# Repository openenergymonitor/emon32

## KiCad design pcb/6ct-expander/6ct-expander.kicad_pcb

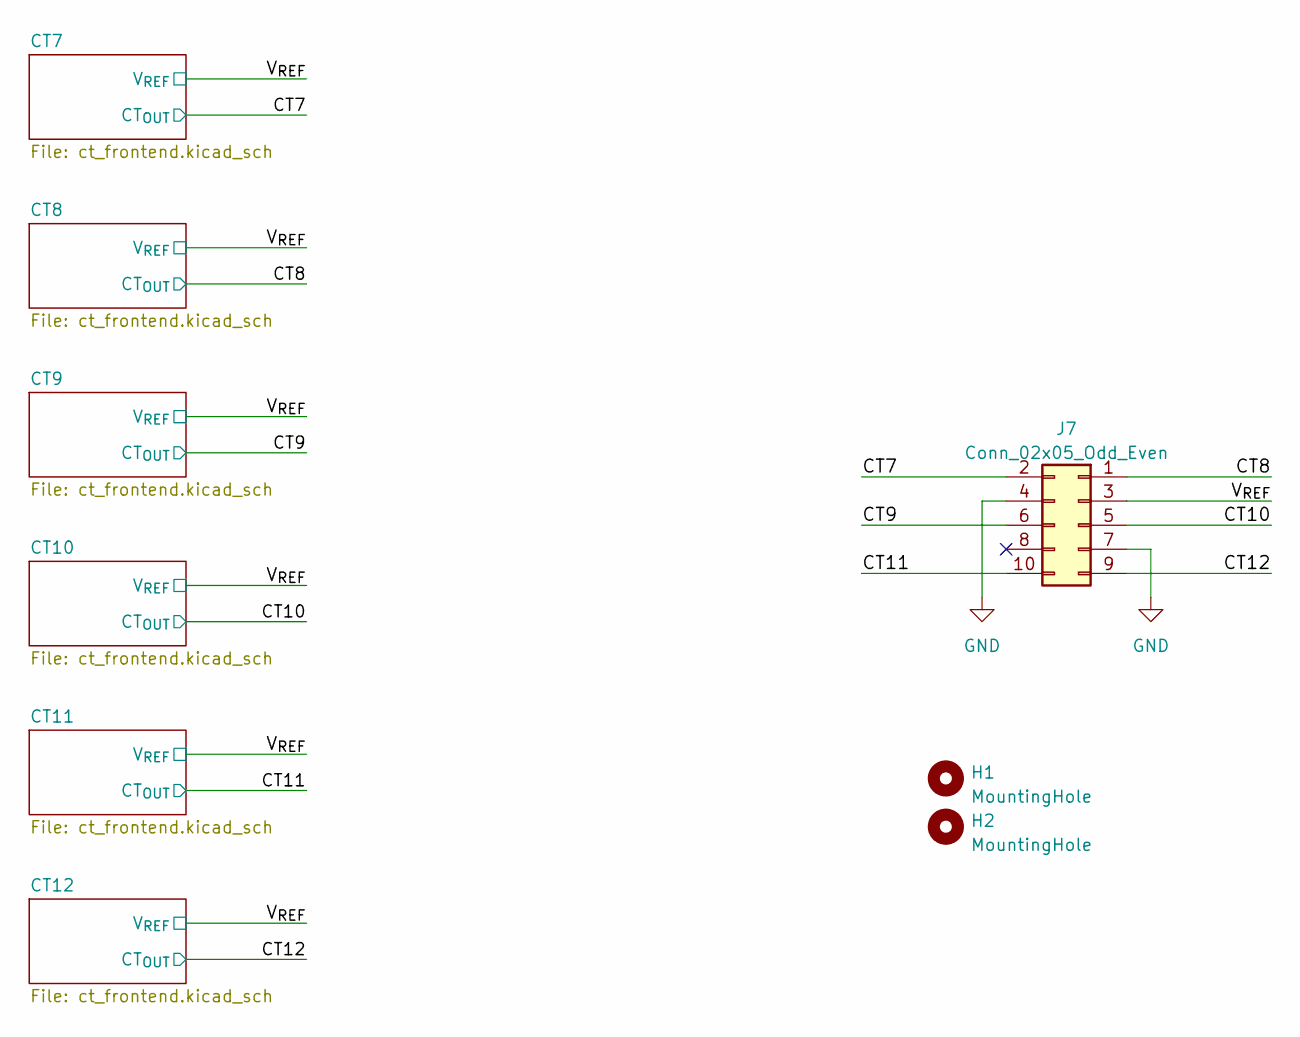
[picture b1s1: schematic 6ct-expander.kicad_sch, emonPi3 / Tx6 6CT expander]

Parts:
H1, H2: MountingHole; MountingHole_2.7mm_M2.5
J7: Conn_02x05_Odd_Even; PinHeader_2x05_P2.54mm_Vertical

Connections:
/CT7: J7.2; also elsewhere on the board
/CT8: J7.1; also elsewhere on the board
/CT9: J7.6; also elsewhere on the board
/CT10: J7.5; also elsewhere on the board
/CT11: J7.10; also elsewhere on the board
/CT12: J7.9; also elsewhere on the board
/V_{REF}: J7.3; also elsewhere on the board
GND: J7.4, J7.7; also elsewhere on the board

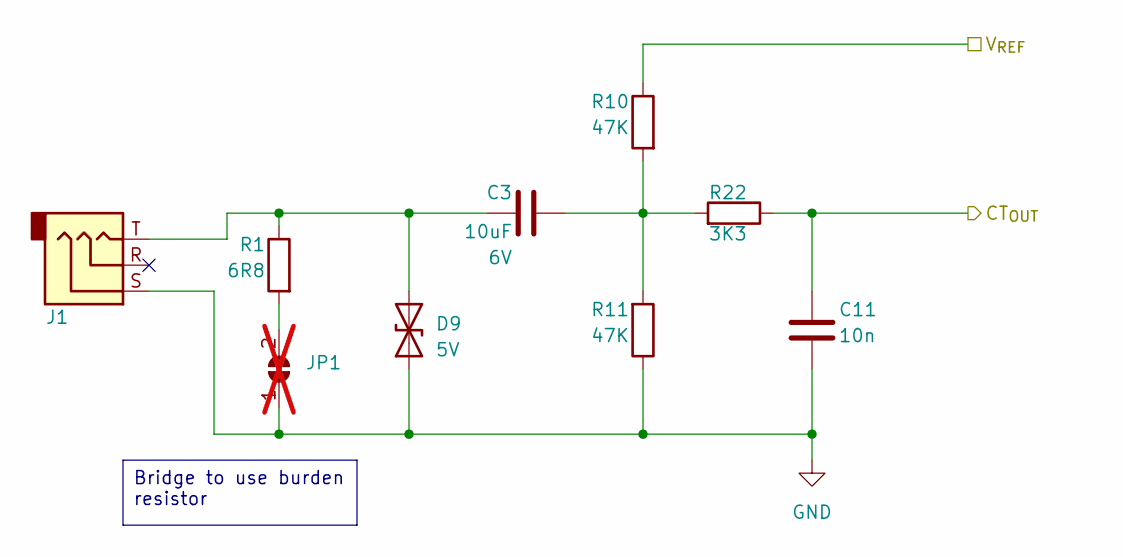
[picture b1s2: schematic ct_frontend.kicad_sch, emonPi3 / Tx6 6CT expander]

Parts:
C3: 10uF; C_0603_1608Metric; Voltage 6V; LCSC C19702
C11: 10n; C_0603_1608Metric; LCSC C57112
D9: 5V; D_SOD-523; MPN DF2B7AE,H3F; Mouser 757-DF2B7AEH3F
J1: SJ-3524-SMT-TR; Jack_3.5mm_CUI_SJ-3524-SMT_Horizontal; LCSC C4991872
JP1: SolderJumper_2_Open; SolderJumper-2_P1.3mm_Open_TrianglePad1.0x1.5mm; not fitted
R1: 6R8; R_1206_3216Metric; LCSC C25345
R10, R11: 47K; R_0603_1608Metric; LCSC C23162
R22: 3K3; R_0603_1608Metric; LCSC C22978

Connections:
/CT7: C11.1, R22.1; also elsewhere on the board
/V_{REF}: R10.1; also elsewhere on the board
GND: C11.2, D9.1 (A1), J1.S, JP1.1 (A), R11.1; also elsewhere on the board
unnamed: C3.2, R10.2, R11.2, R22.2
unnamed: C3.1, D9.2 (A2), J1.T, R1.1
unnamed: JP1.2 (B), R1.2

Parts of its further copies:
C1, C4, C6, C8, C10: 10uF; C_0603_1608Metric; Voltage 6V; LCSC C19702
C2, C5, C7, C9, C12: 10n; C_0603_1608Metric; LCSC C57112
D1, D2, D3, D4, D5: 5V; D_SOD-523; MPN DF2B7AE,H3F; Mouser 757-DF2B7AEH3F
J2, J3, J4, J5, J6: SJ-3524-SMT-TR; Jack_3.5mm_CUI_SJ-3524-SMT_Horizontal; LCSC C4991872
JP2, JP3, JP4, JP5, JP6: SolderJumper_2_Open; SolderJumper-2_P1.3mm_Open_TrianglePad1.0x1.5mm; not fitted
R2, R6: 6R8; R_1206_3216Metric; LCSC C25345
R3, R4, R7, R8, R13, R14, R17, R18, R21, R23: 47K; R_0603_1608Metric; LCSC C23162
R5, R9: 3K3; R_0603_1608Metric; LCSC C22978

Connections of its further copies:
/CT8: C2.1, R5.1; also elsewhere on the board
/CT9: C5.1, R9.1; also elsewhere on the board
/CT10: C7.1; also elsewhere on the board
/CT11: C9.1; also elsewhere on the board
/CT12: C12.1; also elsewhere on the board
/V_{REF}: R3.1, R7.1, R13.1, R17.1, R21.1; also elsewhere on the board
GND: C2.2, C5.2, C7.2, C9.2, C12.2, D1.1 (A1), D2.1 (A1), D3.1 (A1), D4.1 (A1), D5.1 (A1), J2.S, J3.S, J4.S, J5.S, J6.S, JP2.1 (A), JP3.1 (A), JP4.1 (A), JP5.1 (A), JP6.1 (A), R4.1, R8.1, R14.1, R18.1, R23.1; also elsewhere on the board
unnamed: C1.2, R3.2, R4.2, R5.2
unnamed: C4.2, R7.2, R8.2, R9.2
unnamed 11: C6.2, R13.2, R14.2; also elsewhere on the board
unnamed 12: C8.2, R17.2, R18.2; also elsewhere on the board
unnamed 13: C10.2, R21.2, R23.2; also elsewhere on the board
unnamed: C1.1, D1.2 (A2), J2.T, R2.1
unnamed: C4.1, D2.2 (A2), J3.T, R6.1
unnamed 16: C6.1, D3.2 (A2), J4.T; also elsewhere on the board
unnamed 17: C8.1, D4.2 (A2), J5.T; also elsewhere on the board
unnamed 18: C10.1, D5.2 (A2), J6.T; also elsewhere on the board
unnamed: JP2.2 (B), R2.2
unnamed: JP3.2 (B), R6.2
unnamed 23: JP4.2 (B); also elsewhere on the board
unnamed 24: JP5.2 (B); also elsewhere on the board
unnamed 25: JP6.2 (B); also elsewhere on the board

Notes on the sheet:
Bridge to use burden resistor

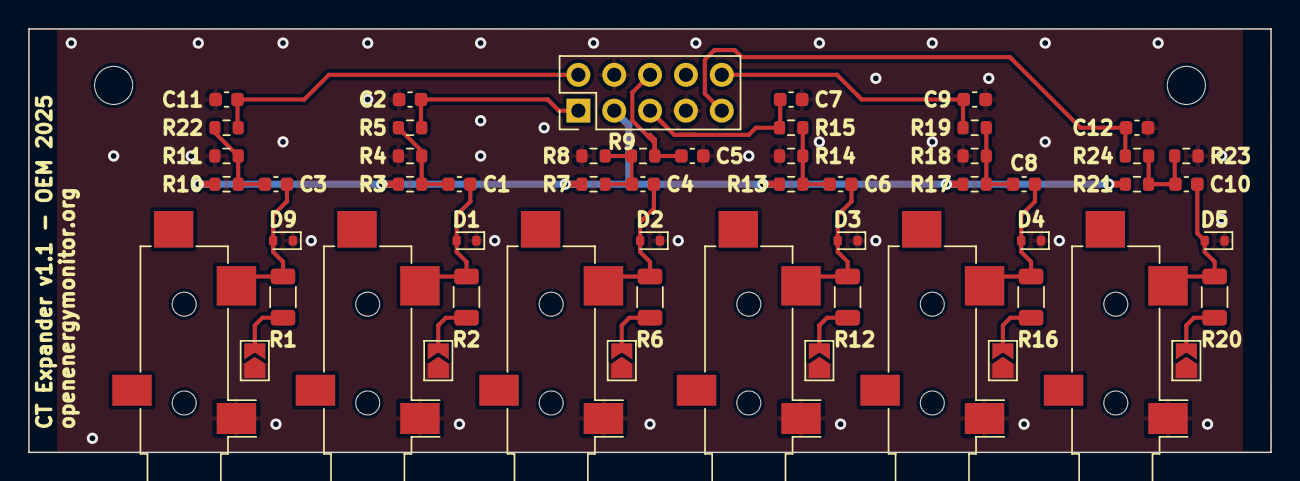
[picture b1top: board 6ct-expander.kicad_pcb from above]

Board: 2 copper layers, 88.0 x 30.0 mm, 57 parts (0 on the bottom side), 26 nets.

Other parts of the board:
R12, R16, R20: 6R8; R_1206_3216Metric
R15, R19, R24: 3K3; R_0603_1608Metric

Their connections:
/CT10: R15.1; also elsewhere on the board
/CT11: R19.1; also elsewhere on the board
/CT12: R24.1; also elsewhere on the board
unnamed 11: R15.2; also elsewhere on the board
unnamed 12: R19.2; also elsewhere on the board
unnamed 13: R24.2; also elsewhere on the board
unnamed 16: R12.1; also elsewhere on the board
unnamed 17: R16.1; also elsewhere on the board
unnamed 18: R20.1; also elsewhere on the board
unnamed 23: R12.2; also elsewhere on the board
unnamed 24: R16.2; also elsewhere on the board
unnamed 25: R20.2; also elsewhere on the board

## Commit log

2025-12-10 [6CT] Mirror connector pins to match emonPi3 pin out
    - Mirrored to emonPi3 pin out facing *down*
    - Also update board information
